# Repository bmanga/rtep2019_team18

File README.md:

# Gait Analysis and Interactive Training 

### Overview
GAIT is about the development of a Raspberry Pi wearable system which analyses the user's walking characteristics and provides targeted training in two separate modes, namely Gait and Training mode.

In Gait mode, data is analysed and classified in real time by use of a deep convolutional neural network which automatically predicts the nature of the gait from the signals received from IMUs mounted on the lower limb and pressure sensors embedded in modified insoles. Training mode offers typical game-based rehabilitation exercises, including weight shifting and calf pushes, and provides both auditory and visual feedback to the user, with games being streamed to an external screen.

This device aims to promote neuroplasticity for motor rehabilitation of stroke patients and may therefore become an auxiliary tool in the recovery of motor functions of stroke survivors. 

Learn more about GAIT on the [Wiki](https://github.com/bmanga/rtep2019_team18/wiki). 

### Prerequisites
* [conan](https://conan.io/) package manager - it can be installed by running ```pip install conan```
  * Make sure you have added the bincrafters remote repository. If not, run:<br/>
 ```conan remote add bincrafters https://api.bintray.com/conan/bincrafters/public-conan```
* [cmake](https://cmake.org/) build system version 3.8 or above

### Build Instructions
From within the cloned repository directory :
* ```mkdir build && cd build```
* ```conan install ..```
* ``` cmake ..```
* ```make```

Or use your favourite ```cmake``` configuration.

### Contributions Guidelines
All code is formatted through `clang-format` according to the `.clang-format` file. `clang-format-6.0` is the recommended version as that's the one used in CI.

The utility script `utils/format_diff_code.sh` (to be run from project root directory) is provided in order to automatically format the changes.

Alternatively, you can copy `utils/pre-commit` into the `.git/hooks` folder to automatically run `clang-format` on commits.

### Follow us!

* [Website](https://gaituofg.wixsite.com/website/)
* [Facebook](https://www.facebook.com/GaitUofG/?modal=admin_todo_tour/) 
* [Twitter](https://twitter.com/GaitUofG/) 
* [Instagram](https://www.instagram.com/gait_uofg/) 
* [YouTube](https://www.youtube.com/channel/UCVHNSSwxwb6042Gx61-woFg/)

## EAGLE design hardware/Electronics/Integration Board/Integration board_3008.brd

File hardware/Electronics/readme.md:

The Electronics folder contains the EAGLE files and data sheets for the IMU PCB and Raspberry Pi Integration Board. Each board is contained within its own folder which also contains images of the PCB's manufactured for our system.

The PCB schematic and EAGLE files conatained in this folder are as follows:
<dl>
  <b>IMU</b>
  <ul>
  <li>Board Schematic</li>
  <li>Board Layout</li>
</ul>
</dl>
<dl>
 <b>Integration Board</b>
  <ul>
  <li>Integration Board Schematic</li>
  <li>Integration Board Layout</li>
</ul>
</dl>

A description of each of these components and relative illustrations can be found in the [Wiki](https://github.com/bmanga/rtep2019_team18/wiki).

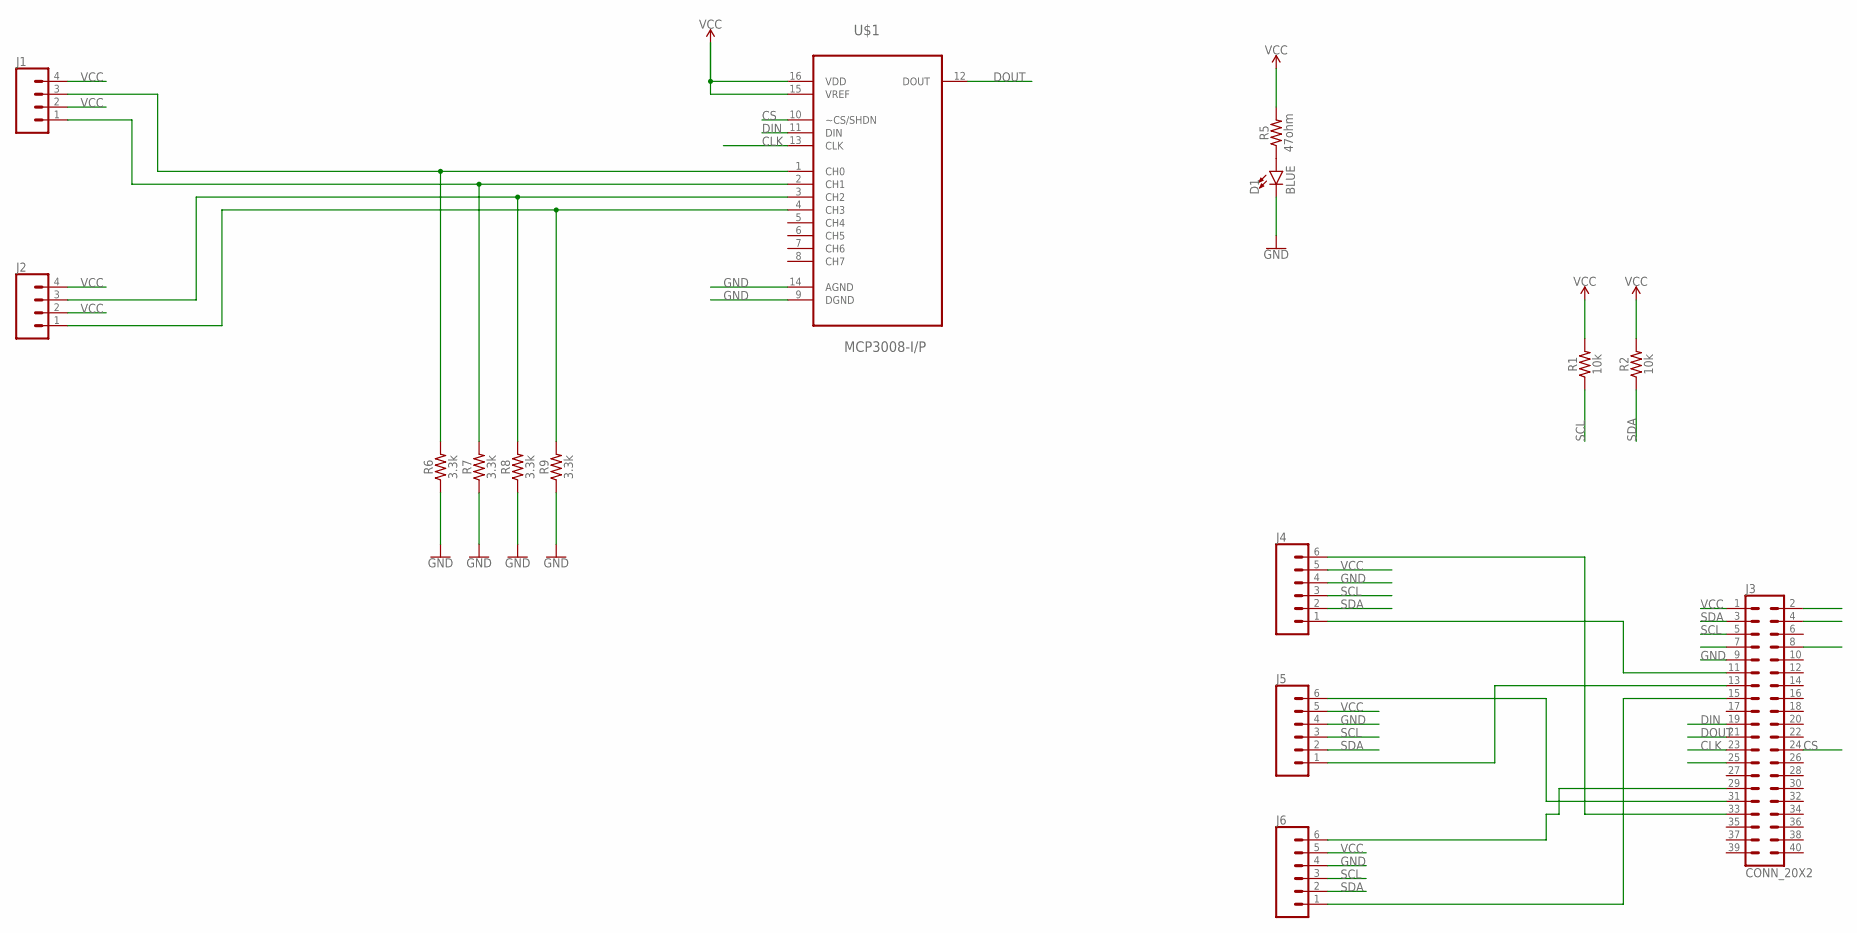
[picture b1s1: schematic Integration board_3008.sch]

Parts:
D1: BLUE; LED-0603
J1, J2: CONN_04PTH; 1X04
J3: CONN_20X2; 2X20
J4, J5, J6: CONN_06SILK_FEMALE_PTH; 1X06
R1, R2: 10k; 0805
R5: 47ohm; 0805
R6, R7, R8, R9: 3.3k; 0805
U$1: MCP3008-I/P; DIP254P762X432-16

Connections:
CLK: J3.23, U$1.13 (CLK)
CS: J3.24, U$1.10 (~CS/SHDN)
DIN: J3.19, U$1.11 (DIN)
DOUT: J3.21, U$1.12 (DOUT)
GND: D1.C, J3.9, J4.4, J5.4, J6.4, R6.1, R7.1, R8.1, R9.1, U$1.9 (DGND), U$1.14 (AGND)
unnamed: J1.3, R6.2, U$1.1 (CH0)
unnamed: J3.11, J4.1
unnamed: J2.3, R8.2, U$1.3 (CH2)
unnamed: J2.1, R9.2, U$1.4 (CH3)
unnamed: J3.13, J5.1
unnamed: J3.29, J6.6
unnamed: J3.31, J5.6
unnamed: D1.A, R5.1
unnamed: J1.1, R7.2, U$1.2 (CH1)
unnamed: J3.33, J4.6
unnamed: J3.15, J6.1
SCL: J3.5, J4.3, J5.3, J6.3, R1.1
SDA: J3.3, J4.2, J5.2, J6.2, R2.1
VCC: J1.2, J1.4, J2.2, J2.4, J3.1, J4.5, J5.5, J6.5, R1.2, R2.2, R5.2, U$1.15 (VREF), U$1.16 (VDD)

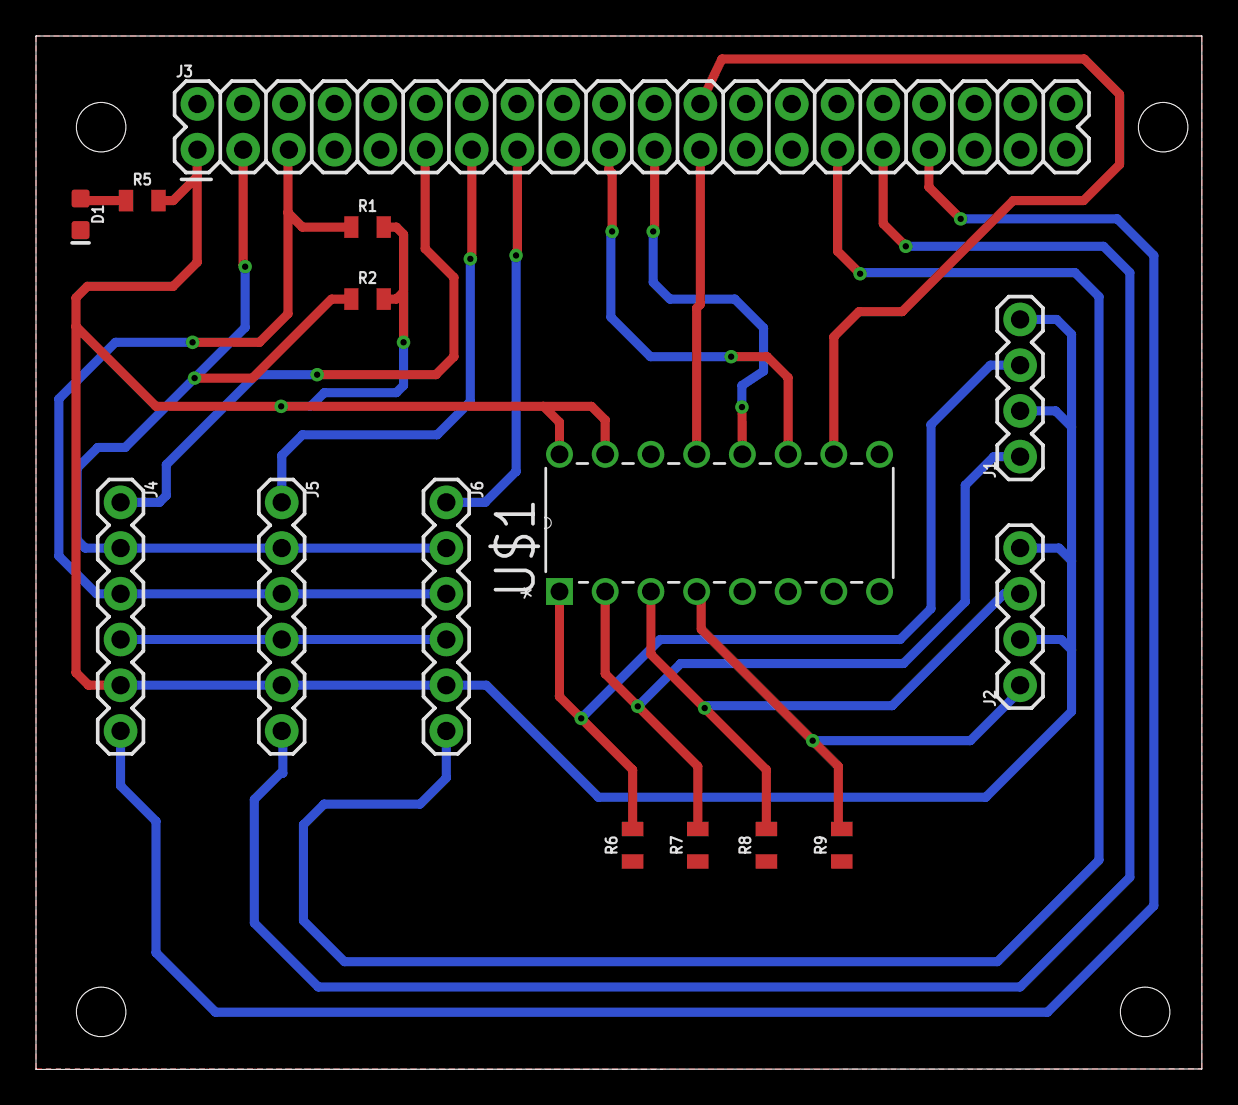
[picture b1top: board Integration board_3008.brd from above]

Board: 2 copper layers, 64.8 x 57.4 mm, 15 parts (0 on the bottom side), 19 nets.

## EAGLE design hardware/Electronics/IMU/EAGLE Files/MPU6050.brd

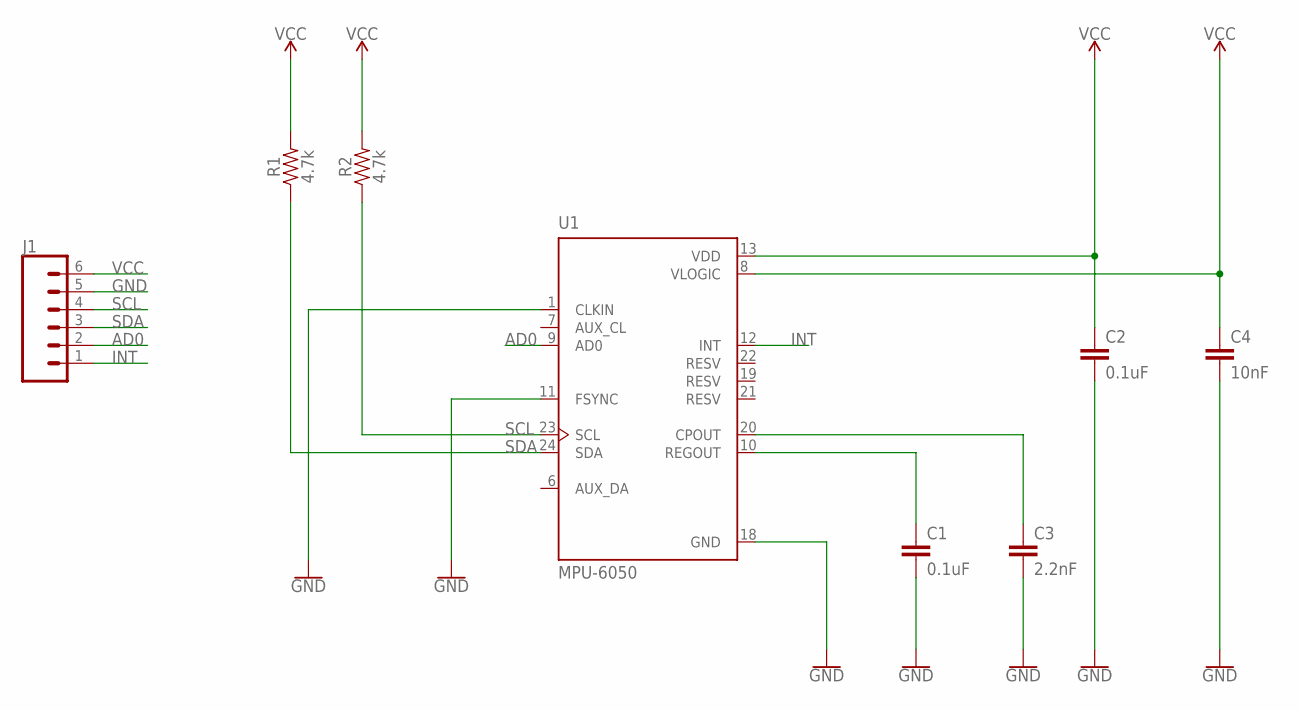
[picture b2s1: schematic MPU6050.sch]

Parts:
C1, C2: 0.1uF; 0805
C3: 2.2nF; 0805
C4: 10nF; 0805
J1: CONN_06NO_SILK_FEMALE_PTH; 1X06_NO_SILK
R1, R2: 4.7k; 0805
U1: MPU-6050; QFN50P400X400X95-24N

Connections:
AD0: J1.2, U1.9 (AD0)
GND: C1.2, C2.2, C3.2, C4.2, J1.5, U1.1 (CLKIN), U1.11 (FSYNC), U1.18 (GND)
INT: J1.1, U1.12 (INT)
unnamed: C1.1, U1.10 (REGOUT)
unnamed: C3.1, U1.20 (CPOUT)
SCL: J1.4, R2.1, U1.23 (SCL)
SDA: J1.3, R1.1, U1.24 (SDA)
VCC: C2.1, C4.1, J1.6, R1.2, R2.2, U1.8 (VLOGIC), U1.13 (VDD)

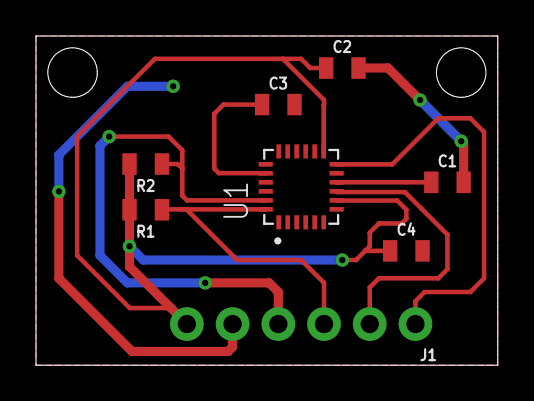
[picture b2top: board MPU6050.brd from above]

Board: 2 copper layers, 25.7 x 18.3 mm, 8 parts (0 on the bottom side), 8 nets.

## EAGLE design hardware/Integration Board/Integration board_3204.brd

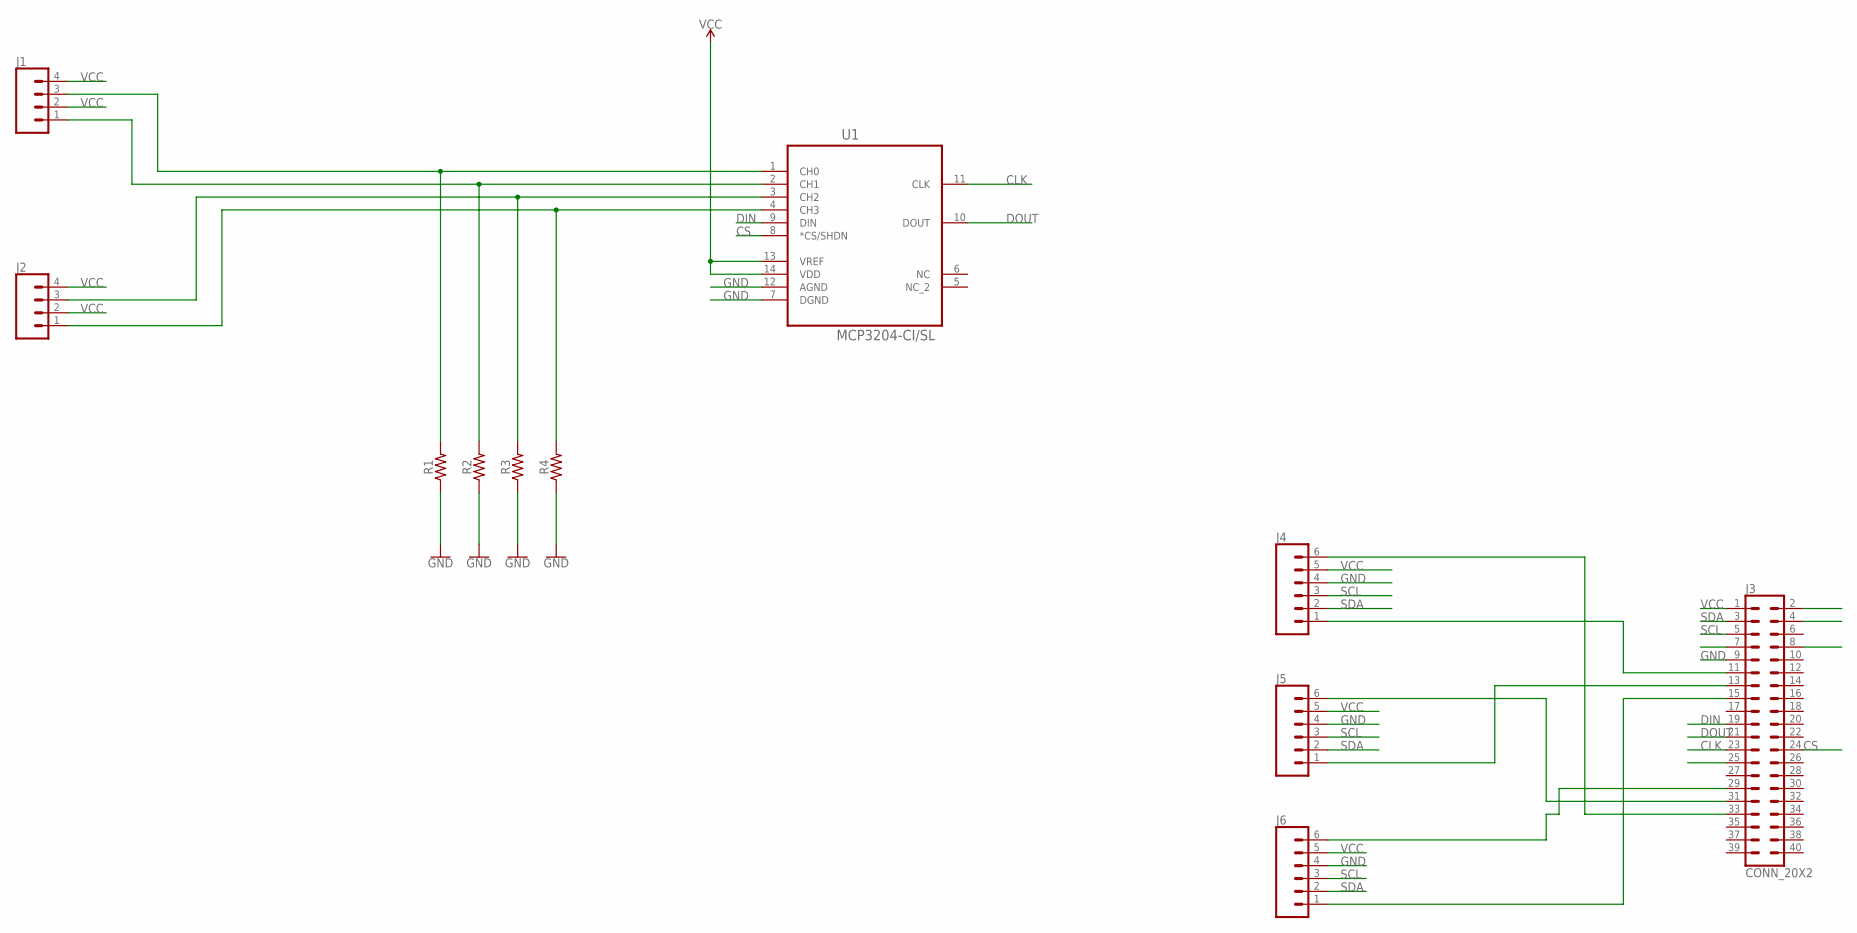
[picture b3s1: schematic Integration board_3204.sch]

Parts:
J1, J2: CONN_04PTH; 1X04
J3: CONN_20X2; 2X20
J4, J5, J6: CONN_06SILK_FEMALE_PTH; 1X06
R1, R2, R3, R4: AXIAL-0.3
U1: MCP3204-CI/SL; SOIC127P600X175-14N

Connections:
CLK: J3.23, U1.11 (CLK)
CS: J3.24, U1.8 (*CS/SHDN)
DIN: J3.19, U1.9 (DIN)
DOUT: J3.21, U1.10 (DOUT)
GND: J3.9, J4.4, J5.4, J6.4, R1.P$1 (1), R2.P$1 (1), R3.P$1 (1), R4.P$1 (1), U1.7 (DGND), U1.12 (AGND)
unnamed: J1.3, R1.P$2 (2), U1.1 (CH0)
unnamed: J3.11, J4.1
unnamed: J2.3, R3.P$2 (2), U1.3 (CH2)
unnamed: J2.1, R4.P$2 (2), U1.4 (CH3)
unnamed: J3.13, J5.1
unnamed: J3.29, J6.6
unnamed: J3.31, J5.6
unnamed: J1.1, R2.P$2 (2), U1.2 (CH1)
unnamed: J3.33, J4.6
unnamed: J3.15, J6.1
SCL: J3.5, J4.3, J5.3, J6.3
SDA: J3.3, J4.2, J5.2, J6.2
VCC: J1.2, J1.4, J2.2, J2.4, J3.1, J4.5, J5.5, J6.5, U1.13 (VREF), U1.14 (VDD)

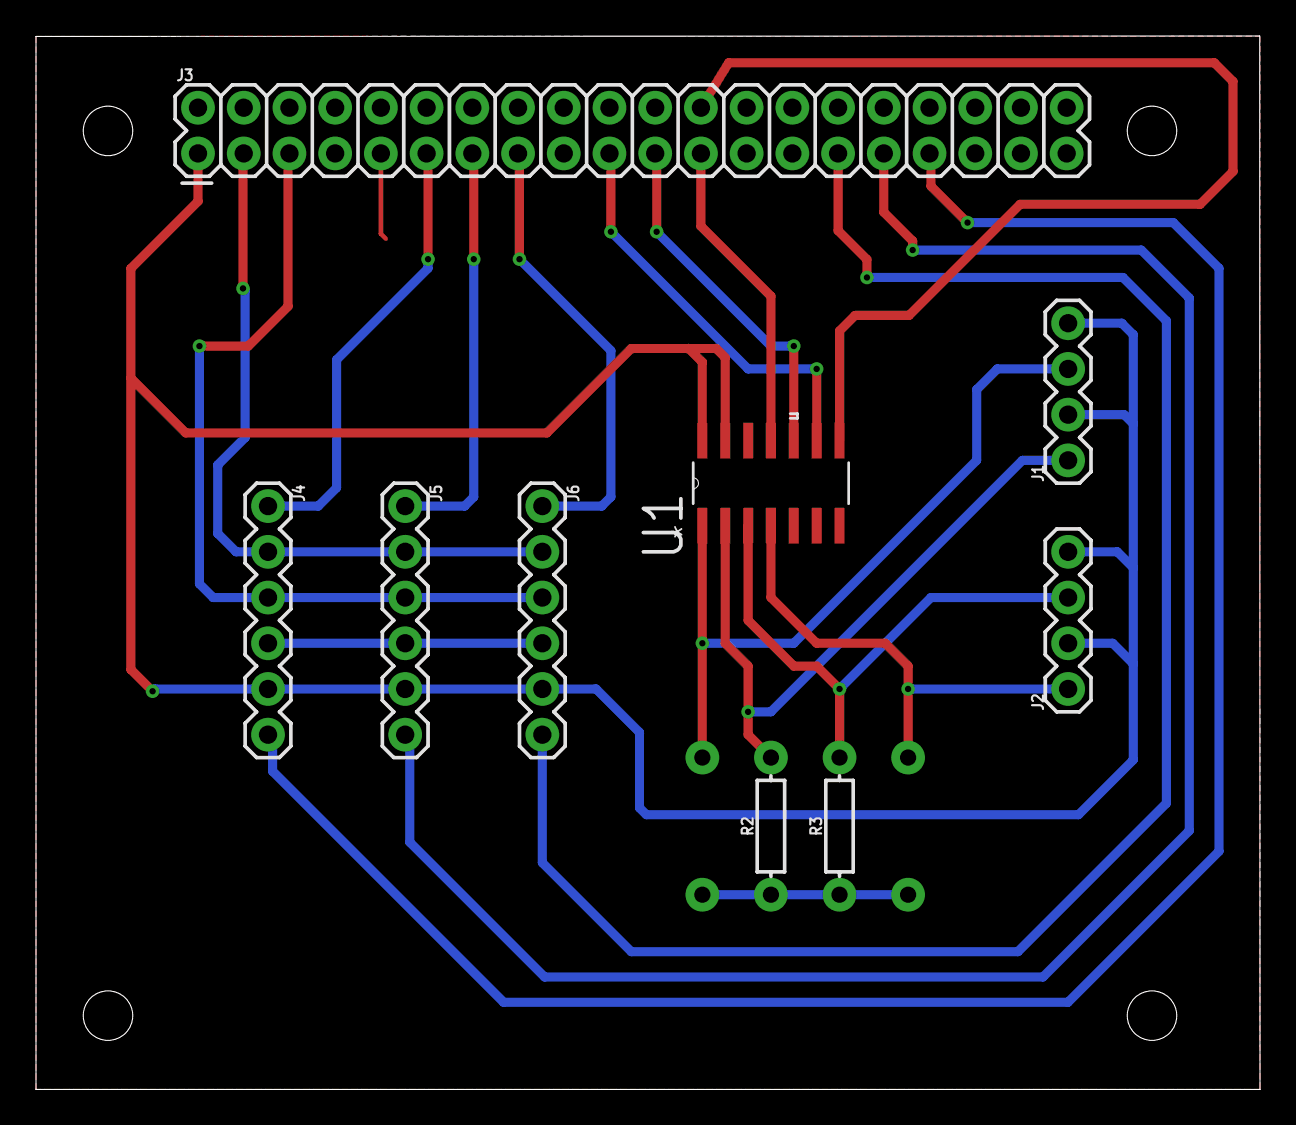
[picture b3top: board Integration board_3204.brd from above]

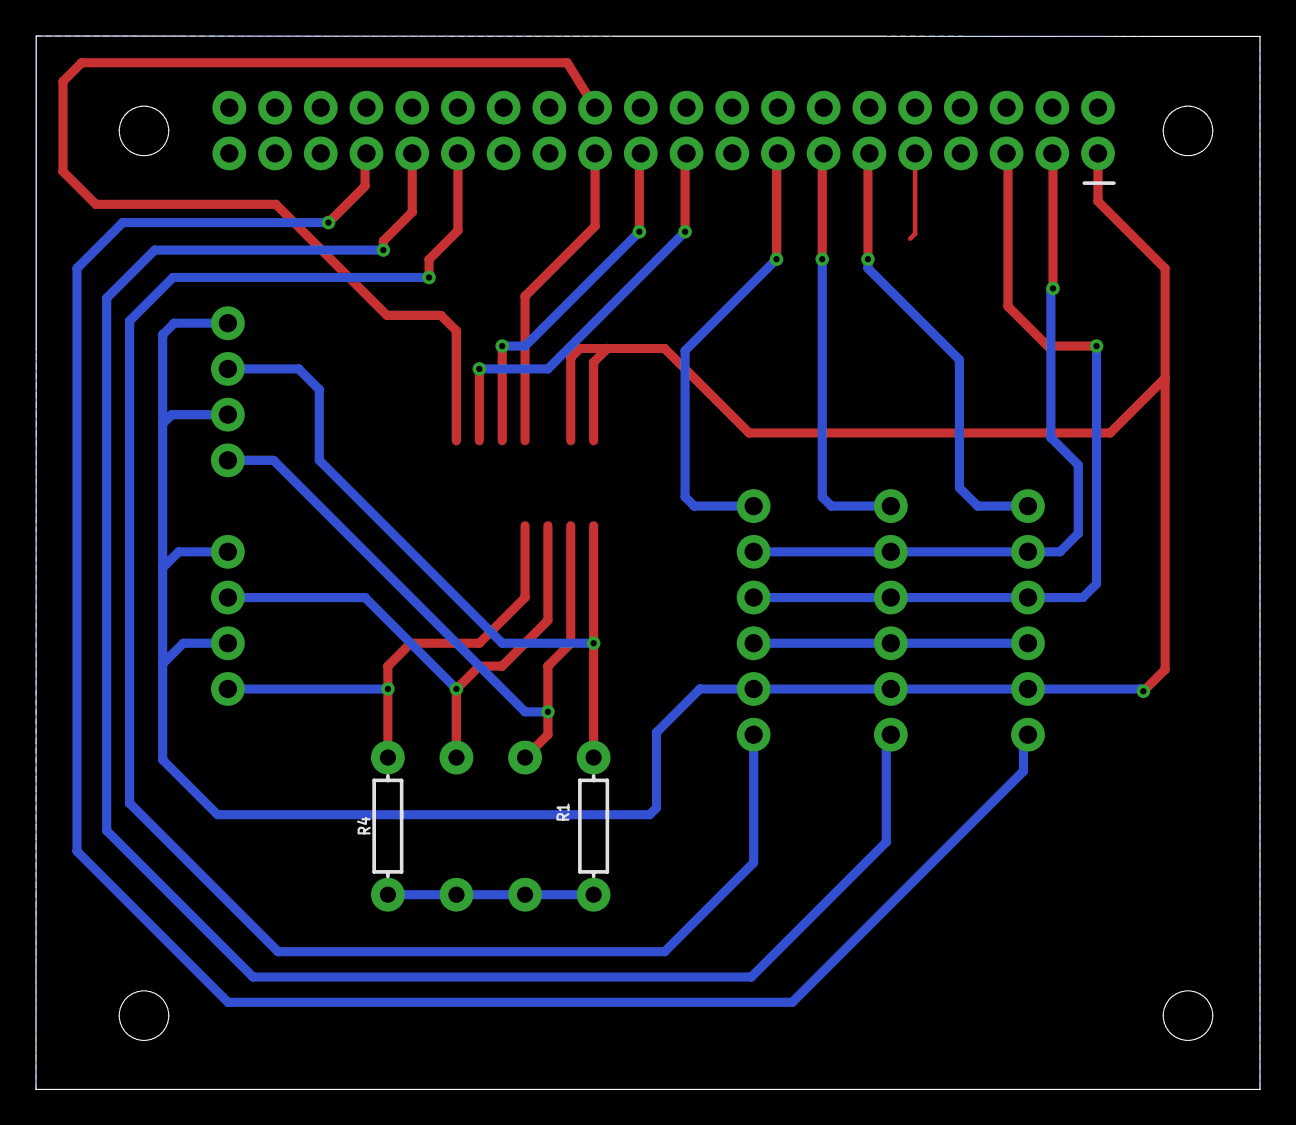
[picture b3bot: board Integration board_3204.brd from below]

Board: 2 copper layers, 68.0 x 58.5 mm, 11 parts (2 on the bottom side), 18 nets.

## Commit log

2019-01-23 Added travis CI
2019-01-23 travis: fix clang build
2019-01-23 travis: temporarily disable clang compiler
2019-01-23 travis: fix clang build.
2019-01-23 bla blah upgrade clang
2019-01-23 travis: fix clang build v2
2019-01-23 travis: re-enable clang build
2019-01-23 travis: add static analysis
2019-01-23 travis: use both virtual cores available when building
2019-01-23 travis: add google clang-format script
2019-01-23 travis: add clang-format check
2019-01-23 added .clang-format file
2019-01-23 testing clang-format
2019-01-23 Update README.md
    Add current build requirements and simple building steps
2019-01-24 added clang-tidy file
2019-01-24 travis: use clang-tidy for static analysis + linting
2019-01-25 travis: cache conan packages
2019-01-26 travis: cache pip
2019-01-29 Update readme
    added brief project description
2019-01-29 Update readme
    Added image, fixed wording
2019-01-29 Update README
    Mention cmake requirement
2019-01-30 Update Readme
    Link to wiki
2019-02-09 travis: update clang-format to version 6.0
2019-02-09 travis: add public-conan remote repository
2019-02-09 travis: set c++11 ABI in conan
2019-02-10 travis: set conan to build missing packages
2019-02-10 travis: force conan bincrafters repo add to exit 0
2019-02-10 telemetry: created library to send telemetry data through websockets
2019-02-10 utils: added clang-format-diff script
2019-02-10 utils: added utility script to format code
2019-02-10 utils: added git hook for pre-commit
2019-02-10 Update README with clang-format information.
2019-02-10 wiringPi: add minimal wiringPi library for i2c comms
2019-02-10 utils: fix pre-commit file
2019-02-12 Library: Add IMU data acquisition library.
2019-02-12 telemetry: add missing PiHiPri file
2019-02-13 tools: add IMUStreamer executable
2019-02-13 tools: add streamreader executable
2019-02-20 tools: add qt gui for imu visualization
2019-02-20 travis: add qt5 package
2019-02-20 libIMU: set read_i2c function private
2019-03-02 libimu: split fd creation from sensor constructor
2019-03-02 libimu: work with multiple sensors
2019-03-02 libimu: cleanup, simplify API
2019-03-06 Set theme jekyll-theme-minimal
2019-03-06 Create CNAME
2019-03-14 lib: added library to use ADC
2019-03-14 tools: added fsr reader
2019-03-14 tools: add mock streamer to test GUI
2019-03-20 tools: remove useless header from QtIMUDisplay
2019-03-20 testing: update travis for qtcharts
2019-03-20 tools: move QtDisplay from QSpline to QLine
2019-03-20 tools:update Qt to handle multiple IMUs and FSRs
2019-03-20 qt gui: added graphs for different sensors
2019-03-20 fix-up
2019-03-20 tools: fix line endings to unix style
2019-03-23 gui: added progress bar implementation
2019-03-23 gui: update files
2019-03-23 gui: added circle widget
2019-03-23 gui: update cmakelists to make xcode happy
2019-03-23 gui: added file for training mode
2019-03-23 visualise new gui
2019-03-23 gui: improve performance by using opengl rendering
2019-03-23 gui: fix bug of axis scrolling by setting range
2019-03-25 qt gui: training mode receiving data
2019-03-25 tools: display target for calf push exercise
2019-03-25 lib: fix telemetry thread
2019-03-25 tools: change layout to include targets in training mode
2019-03-25 tools: receive mock data and display target
2019-04-01 tools: add functionality to save the datapoints as json files
2019-04-01 tools: add tool to visualize data saved in json file
2019-04-01 tools: use fixed representation for the json data timepoints
2019-04-02 tools: update progressbar to emit signals when position is on target
2019-04-02 tools: change colors of circlewidget
2019-04-03 tools: allow navigation in data, zoom in and out
2019-04-03 tools: remove auto copy initialization as it not supported in gcc 6
2019-04-03 tools: set data series in vizualiser as hidden by default
2019-04-07 update widgets and introduce intro screen
2019-04-08 Uploaded IMU and integration board EAGLE files.
2019-04-08 Update README
    Mention the requirement of the bincrafters repo for conan
2019-04-08 Update README
    Fix conan bulletpoint
2019-04-08 tools: Add some gui introductory windows
2019-04-10 utils: added some recorded sensors series
2019-04-10 utils: added python script to analyse and parse savedata
2019-04-10 utils: added pytorch cnn implementation
2019-04-11 Create electronics
2019-04-11 tools: Add GUI intro windows for training mode and update previous
2019-04-11 tools: set savedata directory to be in same directory as executable
2019-04-11 tools: allow to specify path for savedata file
2019-04-11 harware: reorganized folders, added wearables design files
2019-04-11 tools: adjust include path for fsrReader
2019-04-11 tools: add Streamer executable
2019-04-11 lib: split constructor fro IMU reader
2019-04-11 tools: update IMUStreamer for pretty printing and fix packet struct
2019-04-11 manually clang-format files, cleanup commented code
2019-04-11 tools: revert fmt requirement, because it does not play well with clang CI
2019-04-11 lib: remove use of VLA in fsr_reader
2019-04-11 Added README for Wearables
2019-04-11 lib: clang-format fsr_reader
2019-04-11 tools: update tools to also send timepoint
2019-04-12 travis: add required package for mp3 library
2019-04-12 lib: add mp3 playing library
2019-04-12 hardware: include datasheets of IMU chip, FSR, and ADC
2019-04-12 clang formatted mp3 lib
2019-04-12 Update README.md
    New project overview
2019-04-12 Update README.md
    Added links to social media
2019-04-12 Update readmi picture
2019-04-12 Changed Logo in Readme
2019-04-13 Added IMU and Integration board schematic and layout PNG's
2019-04-15 include: add header file for common data types
2019-04-15 tools: removed old binaries
2019-04-15 tools: use common serialization types
2019-04-15 third_party: added directory for 3rd party code, added kfr
2019-04-15 tools: set up basics of the gait-analysis tool
2019-04-15 tools: added gait-analysis dummy executable
2019-04-15 analysis: modified vector data type, add resample function
2019-04-15 tools: created analysis library
2019-04-15 analysis: work-in-progress changes. Use circular buffers to store the incoming data
2019-04-15 third_party: added resampler library
2019-04-15 analysis: save the slice of sensors values from the latest cycle
2019-04-15 third_party, lib: add library for butterworth filtering, analysis code
2019-04-15 third_party: replace kfr library with custom branch to work with gcc-6
2019-04-15 third_party: add DSPFilters library for butterworth filtering
2019-04-15 qt gui: all windows in training mode are now connected
2019-04-15 qt gui: training mode receiving data from sensors
2019-04-15 Edited GUI, now works with realtime data from sensors.
2019-04-15 Added calibration functionality.
2019-04-15 Fixed calibration functionality and added progress bar to calibration window.
2019-04-15 Changed sensor structs to use common_types. Fixed calibrate window done signal.
2019-04-15 Fixing git conflicts.
2019-04-15 Switched saving of left and right in streamer.
2019-04-15 Applied clang formatting to QtGAITGui code.
2019-04-15 Added adaptive scaling progress bars.
2019-04-15 fixme: wip
2019-04-15 Added vocal instructions to GUI.
2019-04-15 Removed fixed progress bar size.
2019-04-15 gui: added working levels
2019-04-16 testing
2019-04-16 Manual Clang formatting applied.
2019-04-16 Added QtSpeech package to travis file.

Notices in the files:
parts and their libraries:
SparkFun-Connectors: Licensing: Creative Commons ShareAlike 4.0 International - https://creativecommons.org/licenses/by-sa/4.0
